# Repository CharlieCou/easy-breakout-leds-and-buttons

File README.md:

# easy-breakout-leds-and-buttons
Eagle files for a breakout board with 8 LEDs and 8 buttons

You can read more on this project at https://hackaday.io/project/7188-8-buttons-8-leds-breakout-board

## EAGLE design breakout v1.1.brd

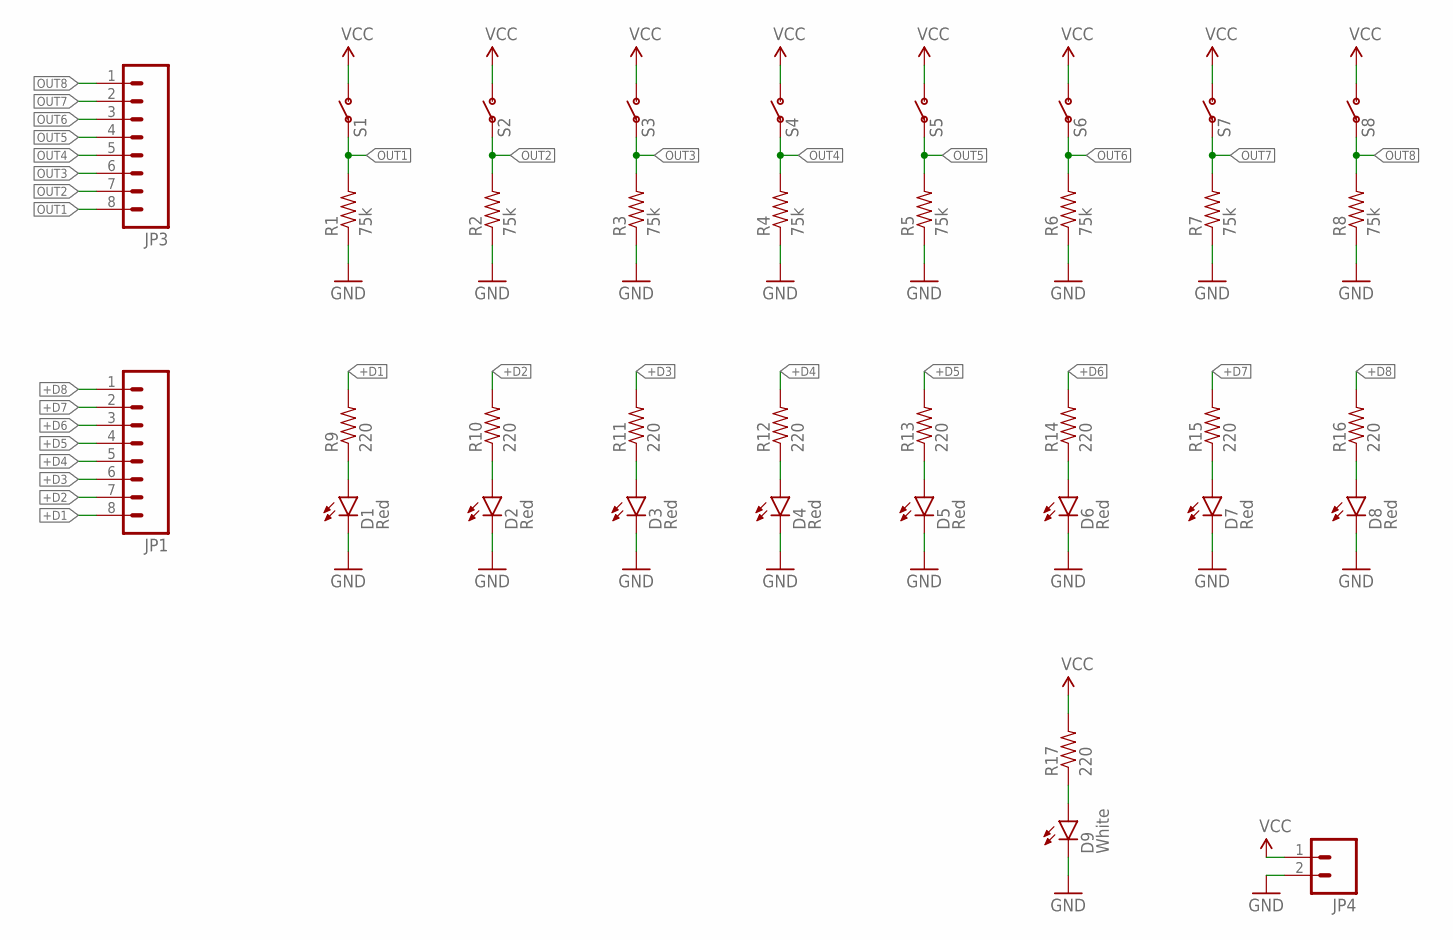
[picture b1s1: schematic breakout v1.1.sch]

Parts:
D1, D2, D3, D4, D5, D6, D7, D8: Red; 0805
D9: White; LED-0603
JP1, JP3: M08; 1X08_ROUND
JP4: M02PTH; 1X02
R1, R2, R3, R4, R5, R6, R7, R8: 75k; 0805
R9, R10, R11, R12, R13, R14, R15, R16, R17: 220; 0805
S1, S2, S3, S4, S5, S6, S7, S8: SWITCH_SPSTSMD; 5.2X5.2X1.5-SMD

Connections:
+D1: JP1.8, R9.2
+D2: JP1.7, R10.2
+D3: JP1.6, R11.2
+D4: JP1.5, R12.2
+D5: JP1.4, R13.2
+D6: JP1.3, R14.2
+D7: JP1.2, R15.2
+D8: JP1.1, R16.2
GND: D1.2 (C), D2.2 (C), D3.2 (C), D4.2 (C), D5.2 (C), D6.2 (C), D7.2 (C), D8.2 (C), D9.C, JP4.2, R1.1, R2.1, R3.1, R4.1, R5.1, R6.1, R7.1, R8.1
unnamed: D1.1 (A), R9.1
unnamed: D2.1 (A), R10.1
unnamed: D3.1 (A), R11.1
unnamed: D4.1 (A), R12.1
unnamed: D5.1 (A), R13.1
unnamed: D6.1 (A), R14.1
unnamed: D7.1 (A), R15.1
unnamed: D8.1 (A), R16.1
unnamed: D9.A, R17.1
OUT1: JP3.8, R1.2, S1.P$3 (2)
OUT2: JP3.7, R2.2, S2.P$3 (2)
OUT3: JP3.6, R3.2, S3.P$3 (2)
OUT4: JP3.5, R4.2, S4.P$3 (2)
OUT5: JP3.4, R5.2, S5.P$3 (2)
OUT6: JP3.3, R6.2, S6.P$3 (2)
OUT7: JP3.2, R7.2, S7.P$3 (2)
OUT8: JP3.1, R8.2, S8.P$3 (2)
VCC: JP4.1, R17.2, S1.P$1 (1), S2.P$1 (1), S3.P$1 (1), S4.P$1 (1), S5.P$1 (1), S6.P$1 (1), S7.P$1 (1), S8.P$1 (1)

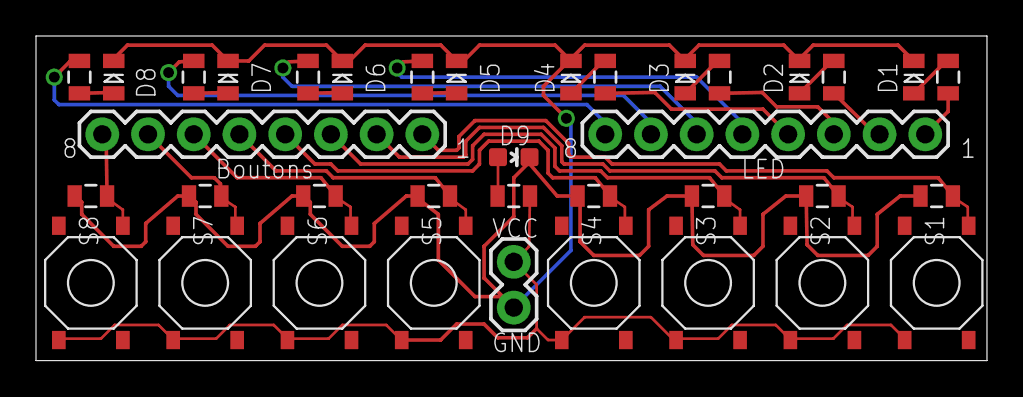
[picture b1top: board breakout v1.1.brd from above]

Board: 2 copper layers, 52.8 x 18.0 mm, 37 parts (0 on the bottom side), 27 nets.

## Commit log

2016-03-02 initial import of eagle files
    Added .brd and .sch files of v1.0 of the board.
2016-03-19 Update README.md
    Added link to the project page on hackaday.io
2016-03-19 Rename breakout.brd to breakout v1.0.brd
2016-03-19 Rename breakout.sch to breakout v1.0.sch
2016-03-19 uploaded eagle files v1.1

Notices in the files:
parts and their libraries:
SparkFun-Connectors: Licensing: Creative Commons ShareAlike 4.0 International - https://creativecommons.org/licenses/by-sa/4.0
